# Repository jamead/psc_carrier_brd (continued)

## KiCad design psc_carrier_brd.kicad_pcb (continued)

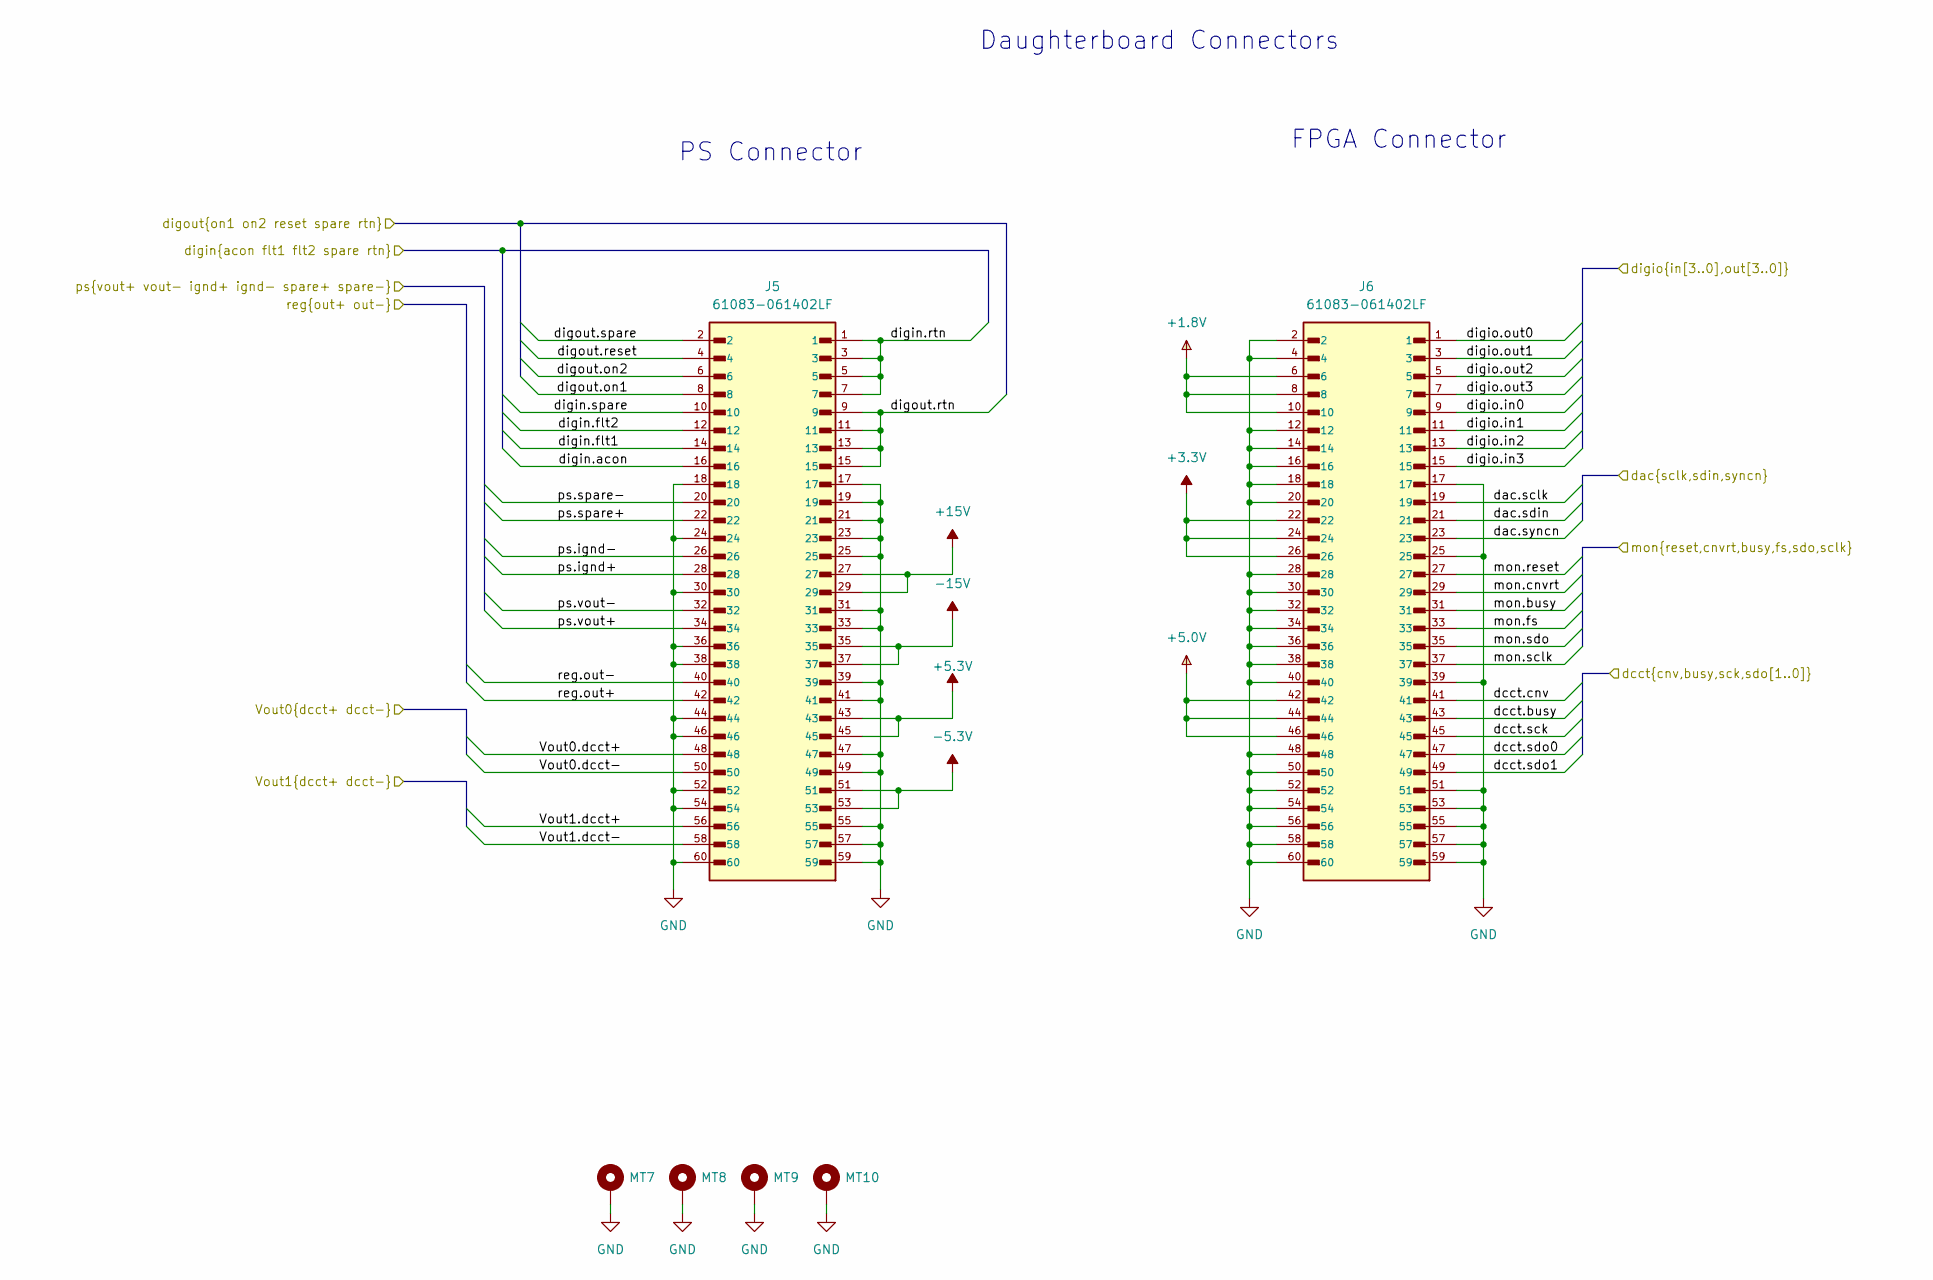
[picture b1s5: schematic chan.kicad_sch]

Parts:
J5, J6: 61083-061402LF; AMPHENOL_61083-061402LF; PARTREV AT
MT7, MT8, MT9, MT10: MountingHole_Pad; MountingHole_3.2mm_M3_Pad_TopBottom

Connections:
+1.8V: J6.6, J6.8, J6.10; also elsewhere on the board
+3.3V: J6.22, J6.24, J6.26; also elsewhere on the board
+5.3V: J5.43, J5.45; also elsewhere on the board
-5.3V: J5.51, J5.53; also elsewhere on the board
/Ch1 Daughterboard/dac.sclk: J6.19; also elsewhere on the board
/Ch1 Daughterboard/dac.sdin: J6.21; also elsewhere on the board
/Ch1 Daughterboard/dac.syncn: J6.23; also elsewhere on the board
/Ch1 Daughterboard/dcct.busy: J6.43; also elsewhere on the board
/Ch1 Daughterboard/dcct.cnv: J6.41; also elsewhere on the board
/Ch1 Daughterboard/dcct.sck: J6.45; also elsewhere on the board
/Ch1 Daughterboard/dcct.sdo0: J6.47; also elsewhere on the board
/Ch1 Daughterboard/dcct.sdo1: J6.49; also elsewhere on the board
/Ch1 Daughterboard/digin.acon: J5.16; also elsewhere on the board
/Ch1 Daughterboard/digin.flt1: J5.14; also elsewhere on the board
/Ch1 Daughterboard/digin.flt2: J5.12; also elsewhere on the board
/Ch1 Daughterboard/digin.rtn: J5.1, J5.3, J5.5, J5.7; also elsewhere on the board
/Ch1 Daughterboard/digin.spare: J5.10; also elsewhere on the board
/Ch1 Daughterboard/digio.in0: J6.9; also elsewhere on the board
/Ch1 Daughterboard/digio.in1: J6.11; also elsewhere on the board
/Ch1 Daughterboard/digio.in2: J6.13; also elsewhere on the board
/Ch1 Daughterboard/digio.in3: J6.15; also elsewhere on the board
/Ch1 Daughterboard/digio.out0: J6.1; also elsewhere on the board
/Ch1 Daughterboard/digio.out1: J6.3; also elsewhere on the board
/Ch1 Daughterboard/digio.out2: J6.5; also elsewhere on the board
/Ch1 Daughterboard/digio.out3: J6.7; also elsewhere on the board
/Ch1 Daughterboard/digout.on1: J5.8; also elsewhere on the board
/Ch1 Daughterboard/digout.on2: J5.6; also elsewhere on the board
/Ch1 Daughterboard/digout.reset: J5.4; also elsewhere on the board
/Ch1 Daughterboard/digout.rtn: J5.9, J5.11, J5.13, J5.15; also elsewhere on the board
/Ch1 Daughterboard/digout.spare: J5.2; also elsewhere on the board
/Ch1 Daughterboard/mon.busy: J6.31; also elsewhere on the board
/Ch1 Daughterboard/mon.cnvrt: J6.29; also elsewhere on the board
/Ch1 Daughterboard/mon.fs: J6.33; also elsewhere on the board
/Ch1 Daughterboard/mon.reset: J6.27; also elsewhere on the board
/Ch1 Daughterboard/mon.sclk: J6.37; also elsewhere on the board
/Ch1 Daughterboard/mon.sdo: J6.35; also elsewhere on the board
/Ch1 Daughterboard/ps.ignd+: J5.28; also elsewhere on the board
/Ch1 Daughterboard/ps.ignd-: J5.26; also elsewhere on the board
/Ch1 Daughterboard/ps.spare+: J5.22; also elsewhere on the board
/Ch1 Daughterboard/ps.spare-: J5.20; also elsewhere on the board
/Ch1 Daughterboard/ps.vout+: J5.34; also elsewhere on the board
/Ch1 Daughterboard/ps.vout-: J5.32; also elsewhere on the board
/Ch1 Daughterboard/reg.out+: J5.42; also elsewhere on the board
/Ch1 Daughterboard/reg.out-: J5.40; also elsewhere on the board

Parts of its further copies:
J9, J10, J12, J13, J15, J16: 61083-061402LF; AMPHENOL_61083-061402LF; PARTREV AT
MT11, MT12, MT13, MT14, MT15, MT16, MT17, MT18, MT19, MT20, MT21, MT22: MountingHole_Pad; MountingHole_3.2mm_M3_Pad_TopBottom

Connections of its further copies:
+1.8V: J10.6, J10.8, J10.10, J13.6, J13.8, J13.10, J16.6, J16.8, J16.10; also elsewhere on the board
+3.3V: J10.22, J10.24, J10.26, J13.22, J13.24, J13.26, J16.22, J16.24, J16.26; also elsewhere on the board
+5.3V: J9.43, J9.45, J12.43, J12.45, J15.43, J15.45; also elsewhere on the board
-5.3V: J9.51, J9.53, J12.51, J12.53, J15.51, J15.53; also elsewhere on the board
/Ch2 Burden Resistor/Vout0.dcct+: J9.48; also elsewhere on the board
/Ch2 Burden Resistor/Vout0.dcct-: J9.50; also elsewhere on the board
/Ch2 Burden Resistor/Vout1.dcct+: J9.56; also elsewhere on the board
/Ch2 Burden Resistor/Vout1.dcct-: J9.58; also elsewhere on the board
/Ch2 Daughterboard/dac.sclk: J10.19; also elsewhere on the board
/Ch2 Daughterboard/dac.sdin: J10.21; also elsewhere on the board
/Ch2 Daughterboard/dac.syncn: J10.23; also elsewhere on the board
/Ch2 Daughterboard/dcct.busy: J10.43; also elsewhere on the board
/Ch2 Daughterboard/dcct.cnv: J10.41; also elsewhere on the board
/Ch2 Daughterboard/dcct.sck: J10.45; also elsewhere on the board
/Ch2 Daughterboard/dcct.sdo0: J10.47; also elsewhere on the board
/Ch2 Daughterboard/dcct.sdo1: J10.49; also elsewhere on the board
/Ch2 Daughterboard/digin.acon: J9.16; also elsewhere on the board
/Ch2 Daughterboard/digin.flt1: J9.14; also elsewhere on the board
/Ch2 Daughterboard/digin.flt2: J9.12; also elsewhere on the board
/Ch2 Daughterboard/digin.rtn: J9.1, J9.3, J9.5, J9.7; also elsewhere on the board
/Ch2 Daughterboard/digin.spare: J9.10; also elsewhere on the board
/Ch2 Daughterboard/digio.in0: J10.9; also elsewhere on the board
/Ch2 Daughterboard/digio.in1: J10.11; also elsewhere on the board
/Ch2 Daughterboard/digio.in2: J10.13; also elsewhere on the board
/Ch2 Daughterboard/digio.in3: J10.15; also elsewhere on the board
/Ch2 Daughterboard/digio.out0: J10.1; also elsewhere on the board
/Ch2 Daughterboard/digio.out1: J10.3; also elsewhere on the board
/Ch2 Daughterboard/digio.out2: J10.5; also elsewhere on the board
/Ch2 Daughterboard/digio.out3: J10.7; also elsewhere on the board
/Ch2 Daughterboard/digout.on1: J9.8; also elsewhere on the board
/Ch2 Daughterboard/digout.on2: J9.6; also elsewhere on the board
/Ch2 Daughterboard/digout.reset: J9.4; also elsewhere on the board
/Ch2 Daughterboard/digout.rtn: J9.9, J9.11, J9.13, J9.15; also elsewhere on the board
/Ch2 Daughterboard/digout.spare: J9.2; also elsewhere on the board
/Ch2 Daughterboard/mon.busy: J10.31; also elsewhere on the board
/Ch2 Daughterboard/mon.cnvrt: J10.29; also elsewhere on the board
/Ch2 Daughterboard/mon.fs: J10.33; also elsewhere on the board
/Ch2 Daughterboard/mon.reset: J10.27; also elsewhere on the board
/Ch2 Daughterboard/mon.sclk: J10.37; also elsewhere on the board
/Ch2 Daughterboard/mon.sdo: J10.35; also elsewhere on the board
/Ch2 Daughterboard/ps.ignd+: J9.28; also elsewhere on the board
/Ch2 Daughterboard/ps.ignd-: J9.26; also elsewhere on the board
/Ch2 Daughterboard/ps.spare+: J9.22; also elsewhere on the board
/Ch2 Daughterboard/ps.spare-: J9.20; also elsewhere on the board
/Ch2 Daughterboard/ps.vout+: J9.34; also elsewhere on the board
/Ch2 Daughterboard/ps.vout-: J9.32; also elsewhere on the board
/Ch2 Daughterboard/reg.out+: J9.42; also elsewhere on the board
/Ch2 Daughterboard/reg.out-: J9.40; also elsewhere on the board
/Ch3 Burden Resistor/Vout0.dcct+: J12.48; also elsewhere on the board
/Ch3 Burden Resistor/Vout0.dcct-: J12.50; also elsewhere on the board
/Ch3 Burden Resistor/Vout1.dcct+: J12.56; also elsewhere on the board
/Ch3 Burden Resistor/Vout1.dcct-: J12.58; also elsewhere on the board
/Ch3 Daughterboard/dac.sclk: J13.19; also elsewhere on the board
/Ch3 Daughterboard/dac.sdin: J13.21; also elsewhere on the board
/Ch3 Daughterboard/dac.syncn: J13.23; also elsewhere on the board
/Ch3 Daughterboard/dcct.busy: J13.43; also elsewhere on the board
/Ch3 Daughterboard/dcct.cnv: J13.41; also elsewhere on the board
/Ch3 Daughterboard/dcct.sck: J13.45; also elsewhere on the board
/Ch3 Daughterboard/dcct.sdo0: J13.47; also elsewhere on the board
/Ch3 Daughterboard/dcct.sdo1: J13.49; also elsewhere on the board
/Ch3 Daughterboard/digin.acon: J12.16; also elsewhere on the board
/Ch3 Daughterboard/digin.flt1: J12.14; also elsewhere on the board
/Ch3 Daughterboard/digin.flt2: J12.12; also elsewhere on the board
/Ch3 Daughterboard/digin.rtn: J12.1, J12.3, J12.5, J12.7; also elsewhere on the board
/Ch3 Daughterboard/digin.spare: J12.10; also elsewhere on the board
/Ch3 Daughterboard/digio.in0: J13.9; also elsewhere on the board
/Ch3 Daughterboard/digio.in1: J13.11; also elsewhere on the board
/Ch3 Daughterboard/digio.in2: J13.13; also elsewhere on the board
/Ch3 Daughterboard/digio.in3: J13.15; also elsewhere on the board
/Ch3 Daughterboard/digio.out0: J13.1; also elsewhere on the board
/Ch3 Daughterboard/digio.out1: J13.3; also elsewhere on the board
/Ch3 Daughterboard/digio.out2: J13.5; also elsewhere on the board
/Ch3 Daughterboard/digio.out3: J13.7; also elsewhere on the board
/Ch3 Daughterboard/digout.on1: J12.8; also elsewhere on the board
/Ch3 Daughterboard/digout.on2: J12.6; also elsewhere on the board
/Ch3 Daughterboard/digout.reset: J12.4; also elsewhere on the board
/Ch3 Daughterboard/digout.rtn: J12.9, J12.11, J12.13, J12.15; also elsewhere on the board
/Ch3 Daughterboard/digout.spare: J12.2; also elsewhere on the board
/Ch3 Daughterboard/mon.busy: J13.31; also elsewhere on the board
/Ch3 Daughterboard/mon.cnvrt: J13.29; also elsewhere on the board
/Ch3 Daughterboard/mon.fs: J13.33; also elsewhere on the board
/Ch3 Daughterboard/mon.reset: J13.27; also elsewhere on the board
/Ch3 Daughterboard/mon.sclk: J13.37; also elsewhere on the board
/Ch3 Daughterboard/mon.sdo: J13.35; also elsewhere on the board
/Ch3 Daughterboard/ps.ignd+: J12.28; also elsewhere on the board
/Ch3 Daughterboard/ps.ignd-: J12.26; also elsewhere on the board
/Ch3 Daughterboard/ps.spare+: J12.22; also elsewhere on the board
/Ch3 Daughterboard/ps.spare-: J12.20; also elsewhere on the board
/Ch3 Daughterboard/ps.vout+: J12.34; also elsewhere on the board
/Ch3 Daughterboard/ps.vout-: J12.32; also elsewhere on the board
/Ch3 Daughterboard/reg.out+: J12.42; also elsewhere on the board
/Ch3 Daughterboard/reg.out-: J12.40; also elsewhere on the board
/Ch4 Burden Resistor/Vout0.dcct+: J15.48; also elsewhere on the board
/Ch4 Burden Resistor/Vout0.dcct-: J15.50; also elsewhere on the board
/Ch4 Burden Resistor/Vout1.dcct+: J15.56; also elsewhere on the board
/Ch4 Burden Resistor/Vout1.dcct-: J15.58; also elsewhere on the board
/Ch4 Daughterboard/dac.sclk: J16.19; also elsewhere on the board
/Ch4 Daughterboard/dac.sdin: J16.21; also elsewhere on the board
/Ch4 Daughterboard/dac.syncn: J16.23; also elsewhere on the board
/Ch4 Daughterboard/dcct.busy: J16.43; also elsewhere on the board
/Ch4 Daughterboard/dcct.cnv: J16.41; also elsewhere on the board
/Ch4 Daughterboard/dcct.sck: J16.45; also elsewhere on the board
/Ch4 Daughterboard/dcct.sdo0: J16.47; also elsewhere on the board
/Ch4 Daughterboard/dcct.sdo1: J16.49; also elsewhere on the board
/Ch4 Daughterboard/digin.acon: J15.16; also elsewhere on the board
/Ch4 Daughterboard/digin.flt1: J15.14; also elsewhere on the board
/Ch4 Daughterboard/digin.flt2: J15.12; also elsewhere on the board
/Ch4 Daughterboard/digin.rtn: J15.1, J15.3, J15.5, J15.7; also elsewhere on the board
/Ch4 Daughterboard/digin.spare: J15.10; also elsewhere on the board
/Ch4 Daughterboard/digio.in0: J16.9; also elsewhere on the board
/Ch4 Daughterboard/digio.in1: J16.11; also elsewhere on the board
/Ch4 Daughterboard/digio.in2: J16.13; also elsewhere on the board
/Ch4 Daughterboard/digio.in3: J16.15; also elsewhere on the board
/Ch4 Daughterboard/digio.out0: J16.1; also elsewhere on the board
/Ch4 Daughterboard/digio.out1: J16.3; also elsewhere on the board
/Ch4 Daughterboard/digio.out2: J16.5; also elsewhere on the board
/Ch4 Daughterboard/digio.out3: J16.7; also elsewhere on the board
/Ch4 Daughterboard/digout.on1: J15.8; also elsewhere on the board
/Ch4 Daughterboard/digout.on2: J15.6; also elsewhere on the board
/Ch4 Daughterboard/digout.reset: J15.4; also elsewhere on the board
/Ch4 Daughterboard/digout.rtn: J15.9, J15.11, J15.13, J15.15; also elsewhere on the board
/Ch4 Daughterboard/digout.spare: J15.2; also elsewhere on the board
/Ch4 Daughterboard/mon.busy: J16.31; also elsewhere on the board
/Ch4 Daughterboard/mon.cnvrt: J16.29; also elsewhere on the board
/Ch4 Daughterboard/mon.fs: J16.33; also elsewhere on the board
/Ch4 Daughterboard/mon.reset: J16.27; also elsewhere on the board
/Ch4 Daughterboard/mon.sclk: J16.37; also elsewhere on the board
/Ch4 Daughterboard/mon.sdo: J16.35; also elsewhere on the board
/Ch4 Daughterboard/ps.ignd+: J15.28; also elsewhere on the board
/Ch4 Daughterboard/ps.ignd-: J15.26; also elsewhere on the board
/Ch4 Daughterboard/ps.spare+: J15.22; also elsewhere on the board
/Ch4 Daughterboard/ps.spare-: J15.20; also elsewhere on the board
/Ch4 Daughterboard/ps.vout+: J15.34; also elsewhere on the board
/Ch4 Daughterboard/ps.vout-: J15.32; also elsewhere on the board
/Ch4 Daughterboard/reg.out+: J15.42; also elsewhere on the board
/Ch4 Daughterboard/reg.out-: J15.40; also elsewhere on the board

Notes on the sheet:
Daughterboard Connectors
FPGA Connector
PS Connector

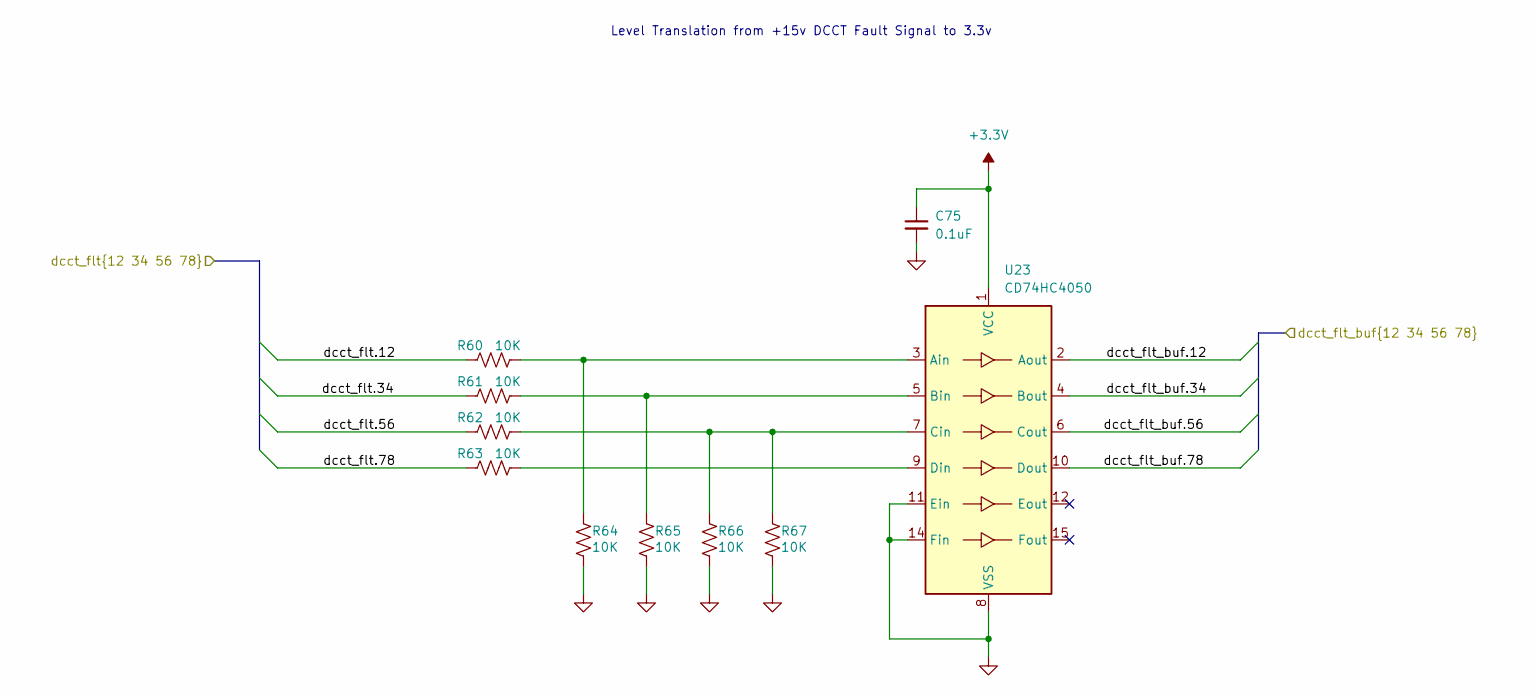
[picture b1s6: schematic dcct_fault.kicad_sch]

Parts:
C75: 0.1uF; C_0402_1005Metric
R60, R61, R62, R63, R64, R65, R66, R67: 10K; R_0402_1005Metric; Tolerance 1%
U23: CD74HC4050; PW16; MFG_PN CD74HC4050PWR

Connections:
+3.3V: C75.1, U23.1 (VCC); also elsewhere on the board
/DCCT Fault Logic/dcct_flt.12: R60.1; also elsewhere on the board
/DCCT Fault Logic/dcct_flt.34: R61.1; also elsewhere on the board
/DCCT Fault Logic/dcct_flt.56: R62.1; also elsewhere on the board
/DCCT Fault Logic/dcct_flt.78: R63.1; also elsewhere on the board
/DCCT Fault Logic/dcct_flt_buf.12: U23.2 (Aout); also elsewhere on the board
/DCCT Fault Logic/dcct_flt_buf.34: U23.4 (Bout); also elsewhere on the board
/DCCT Fault Logic/dcct_flt_buf.56: U23.6 (Cout); also elsewhere on the board
/DCCT Fault Logic/dcct_flt_buf.78: U23.10 (Dout); also elsewhere on the board
unnamed: R60.2, R64.1, U23.3 (Ain)
unnamed: R61.2, R65.1, U23.5 (Bin)
unnamed: R62.2, R66.1, R67.1, U23.7 (Cin)
unnamed: R63.2, U23.9 (Din)

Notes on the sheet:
Level Translation from +15v DCCT Fault Signal to 3.3v

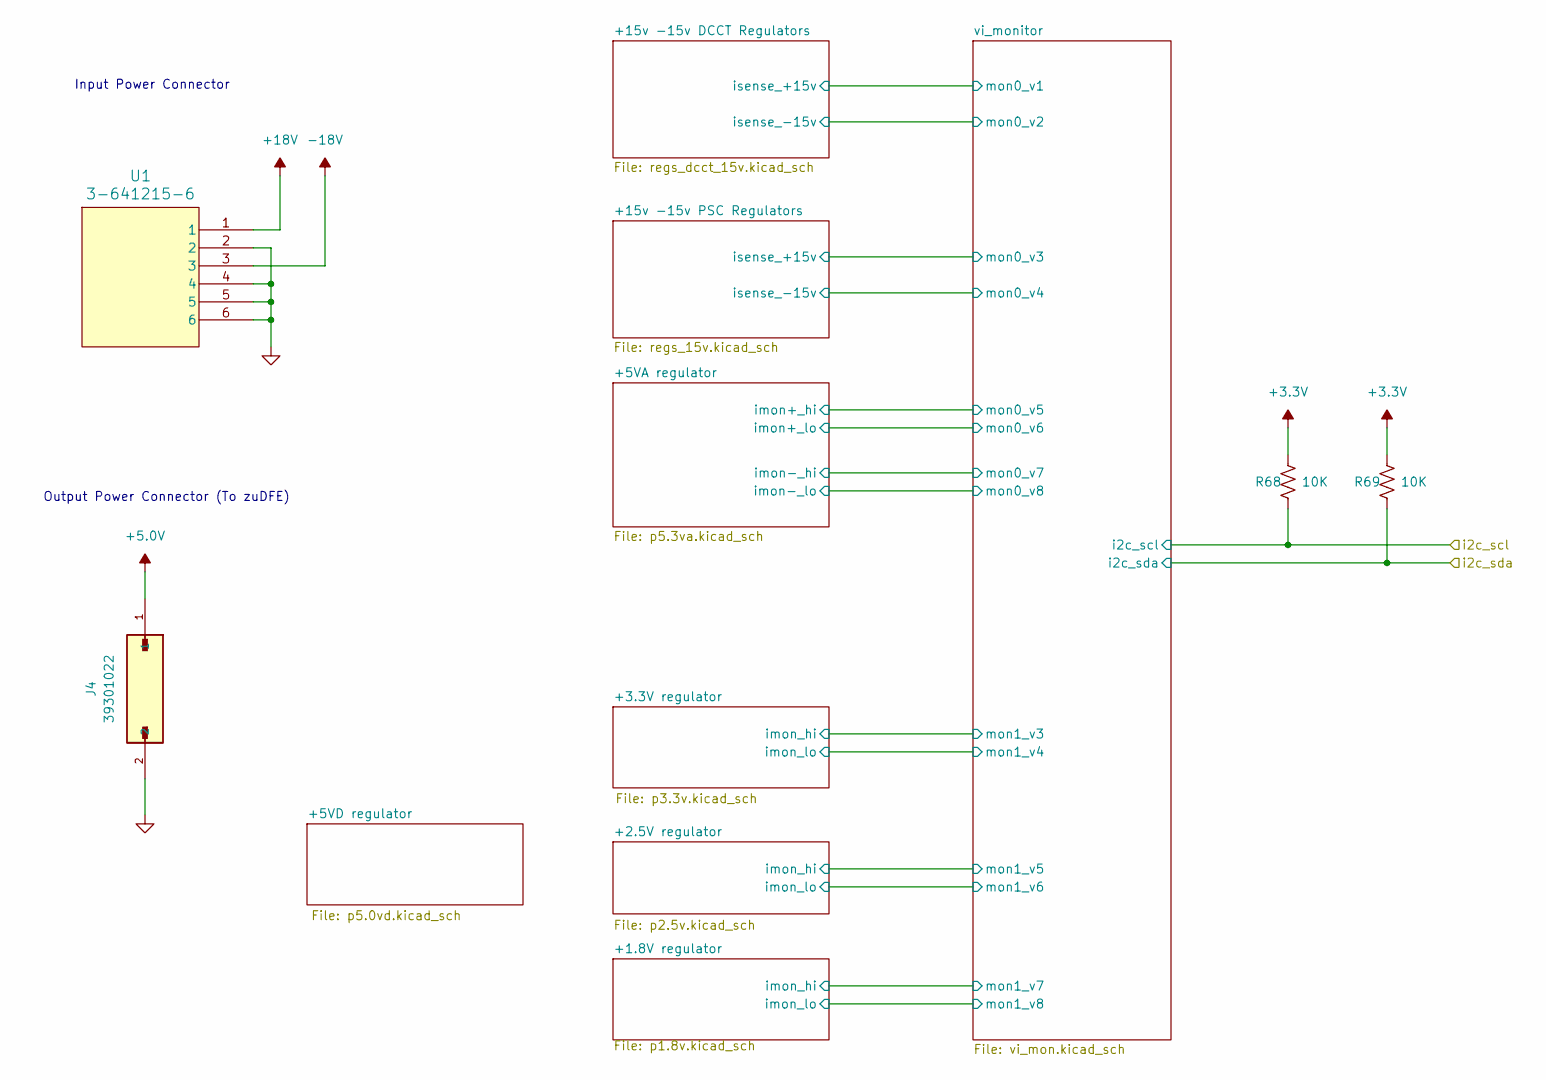
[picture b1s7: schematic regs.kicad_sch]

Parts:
J4: 39301022; MOLEX_39301022; PARTREV A
R68, R69: 10K; R_0402_1005Metric; Tolerance 1%
U1: 3-641215-6; 3-641215-6_TYC

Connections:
+3.3V: R68.1, R69.1; also elsewhere on the board
/regulators/i2c_scl: R68.2; also elsewhere on the board
/regulators/i2c_sda: R69.2; also elsewhere on the board

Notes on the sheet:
Output Power Connector (To zuDFE)
Input Power Connector

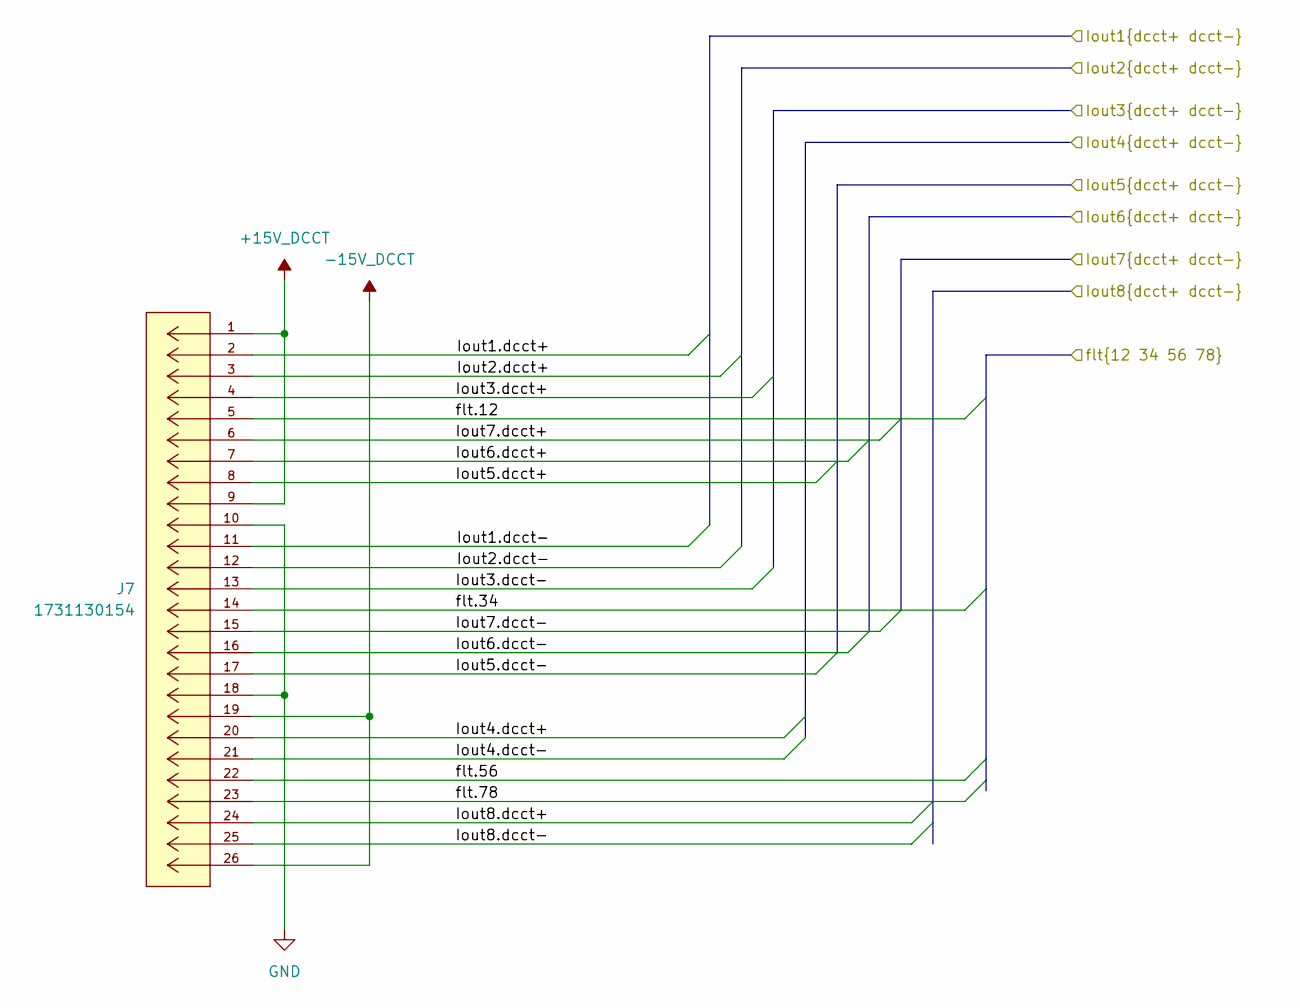
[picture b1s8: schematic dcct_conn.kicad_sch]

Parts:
J7: 1731130154; CONN_F15-26P135G0-5979_MOL; MANUFACTURER_PART_NUMBER 1731130154

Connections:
+15V_DCCT: J7.1, J7.9; also elsewhere on the board
-15V_DCCT: J7.19, J7.26; also elsewhere on the board
/Ch1 Burden Resistor/Iin0.dcct-: J7.11; also elsewhere on the board
/Ch2 Burden Resistor/Iin0.dcct+: J7.4; also elsewhere on the board
/Ch2 Burden Resistor/Iin0.dcct-: J7.13; also elsewhere on the board
/Ch2 Burden Resistor/Iin1.dcct+: J7.20; also elsewhere on the board
/Ch2 Burden Resistor/Iin1.dcct-: J7.21; also elsewhere on the board
/Ch3 Burden Resistor/Iin0.dcct+: J7.8; also elsewhere on the board
/Ch3 Burden Resistor/Iin0.dcct-: J7.17; also elsewhere on the board
/Ch3 Burden Resistor/Iin1.dcct+: J7.7; also elsewhere on the board
/Ch3 Burden Resistor/Iin1.dcct-: J7.16; also elsewhere on the board
/Ch4 Burden Resistor/Iin0.dcct+: J7.6; also elsewhere on the board
/Ch4 Burden Resistor/Iin0.dcct-: J7.15; also elsewhere on the board
/Ch4 Burden Resistor/Iin1.dcct+: J7.24; also elsewhere on the board
/Ch4 Burden Resistor/Iin1.dcct-: J7.25; also elsewhere on the board
/DCCT Fault Logic/dcct_flt.12: J7.5; also elsewhere on the board
/DCCT Fault Logic/dcct_flt.34: J7.14; also elsewhere on the board
/DCCT Fault Logic/dcct_flt.56: J7.22; also elsewhere on the board
/DCCT Fault Logic/dcct_flt.78: J7.23; also elsewhere on the board

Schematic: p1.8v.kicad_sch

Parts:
C34, C35, C38: 10uF; C_0603_1608Metric; Voltage 25V
C36, C37: 0.1uF; C_0402_1005Metric
C39: 100uF; C_1206_3216Metric; Voltage 10V
L4: LSMGG160808T331RG; IND_LSMG_160808_TAY
R20: 0; R_0402_1005Metric; Tolerance 1%
R21: 18.0K; R_0402_1005Metric; Tolerance 1%
R22: KRL2012E-M-R220-F-T5; RESC1220X70N
U9: LT3045xDD; DFN-10-1EP_3x3mm_P0.5mm_EP1.65x2.38mm

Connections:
+1.8V: R22.2, U9.9 (OUTS); also elsewhere on the board
/regulators/+1.8V regulator/imon_hi: C37.1, C38.1, C39.1, R22.1, U9.10 (OUT); also elsewhere on the board
unnamed: C35.1, C36.1, L4.1, U9.1 (IN), U9.2 (IN), U9.3 (EN/UV), U9.6 (PGFB)
unnamed: R20.1, U9.5 (ILIM)
unnamed: R21.1, U9.7 (SET)

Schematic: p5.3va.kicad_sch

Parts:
C16, C17, C18, C20, C22, C25: 10uF; C_0603_1608Metric; Voltage 25V
C19, C21, C23, C24: 0.1uF; C_0402_1005Metric
C26, C27: 100uF; C_1206_3216Metric; Voltage 10V
L1, L2: LSMGG160808T331RG; IND_LSMG_160808_TAY
R11: 0; R_0402_1005Metric; Tolerance 1%
R12: 53K; R_0402_1005Metric; Tolerance 1%
R13, R14: KRL2012E-M-R220-F-T5; RESC1220X70N
R15: 11.4K; R_0402_1005Metric; Tolerance 1%
R16: 1.0K; R_0402_1005Metric; Tolerance 1%
U6: LT3015EDDPBF; DFN-8_DD; MANUFACTURER_PART_NUMBER lt3015edd#pbf
U7: LT3045xDD; DFN-10-1EP_3x3mm_P0.5mm_EP1.65x2.38mm

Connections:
+5.3V: R14.2, U7.9 (OUTS); also elsewhere on the board
-5.3V: R13.2, R15.1; also elsewhere on the board
/regulators/+5VA regulator/+5.3Vout: C23.1, C25.1, C27.1, R14.1, U7.10 (OUT); also elsewhere on the board
/regulators/+5VA regulator/-5.3Vout: C22.1, C24.1, C26.1, R13.1, U6.7 (OUT), U6.8 (OUT); also elsewhere on the board
unnamed: C18.1, C19.1, L1.1, U6.1 (IN), U6.2 (IN), U6.3 (*SHDN), U6.9 (IN)
unnamed: R15.2, R16.1, U6.6 (SENSE/ADJ)
unnamed: C20.1, C21.1, L2.1, U7.1 (IN), U7.2 (IN), U7.3 (EN/UV), U7.6 (PGFB)
unnamed: R11.1, U7.5 (ILIM)
unnamed: R12.1, U7.7 (SET)

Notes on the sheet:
Expected Iout = 9mA*4 + 5mA*4 = 56mA Pd = 56mA * 9.7v = 0.54W deltaT ~ 25 C

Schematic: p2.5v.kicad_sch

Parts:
C40, C41, C44: 10uF; C_0603_1608Metric; Voltage 25V
C42, C43: 0.1uF; C_0402_1005Metric
C45: 100uF; C_1206_3216Metric; Voltage 10V
L5: LSMGG160808T331RG; IND_LSMG_160808_TAY
R23: 0; R_0402_1005Metric; Tolerance 1%
R24: 24.9K; R_0402_1005Metric; Tolerance 1%
R25: KRL2012E-M-R220-F-T5; RESC1220X70N
U10: LT3045xDD; DFN-10-1EP_3x3mm_P0.5mm_EP1.65x2.38mm

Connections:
+2.5V: R25.2, U10.9 (OUTS); also elsewhere on the board
/regulators/+2.5V regulator/imon_hi: C43.1, C44.1, C45.1, R25.1, U10.10 (OUT); also elsewhere on the board
unnamed: C41.1, C42.1, L5.1, U10.1 (IN), U10.2 (IN), U10.3 (EN/UV), U10.6 (PGFB)
unnamed: R23.1, U10.5 (ILIM)
unnamed: R24.1, U10.7 (SET)

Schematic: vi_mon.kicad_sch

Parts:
C57, C58, C59: 0.1uF; C_0402_1005Metric
R36, R38, R40, R43, R45, R47: 9K; R_0402_1005Metric; Tolerance 1%
R37, R39, R41: 1K; R_0402_1005Metric; Tolerance 1%
R42, R44, R46: 9.56K; R_0402_1005Metric; Tolerance 1%
R48, R49: 4.99K; R_0402_1005Metric; Tolerance 1%
U12, U13, U14: LTC2991CMS_TRPBF; MSOP-16_MS; MANUFACTURER_PART_NUMBER ltc2991cms#pbf

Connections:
+1.8V: U12.8 (V8); also elsewhere on the board
+2.5V: U12.6 (V6); also elsewhere on the board
+3.3V: C57.1, C58.1, C59.1, R48.1, R49.1, U12.4 (V4), U12.16 (VCC), U13.16 (VCC), U14.16 (VCC); also elsewhere on the board
+5.3V: U14.6 (V6); also elsewhere on the board
+15V_DCCT: R40.1; also elsewhere on the board
-5.3V: U14.8 (V8); also elsewhere on the board
-15V_DCCT: R46.1; also elsewhere on the board
/regulators/+1.8V regulator/imon_hi: U12.7 (V7); also elsewhere on the board
/regulators/+2.5V regulator/imon_hi: U12.5 (V5); also elsewhere on the board
/regulators/+3.3V regulator/imon_hi: U12.3 (V3); also elsewhere on the board
/regulators/+5VA regulator/+5.3Vout: U14.5 (V5); also elsewhere on the board
/regulators/+5VA regulator/-5.3Vout: U14.7 (V7); also elsewhere on the board
/regulators/+15v -15v DCCT Regulators/isense_+15v: U14.1 (V1); also elsewhere on the board
/regulators/+15v -15v DCCT Regulators/isense_-15v: U14.2 (V2); also elsewhere on the board
/regulators/+15v -15v PSC Regulators/isense_+15v: U14.3 (V3); also elsewhere on the board
/regulators/+15v -15v PSC Regulators/isense_-15v: U14.4 (V4); also elsewhere on the board
/regulators/i2c_scl: U12.11 (SCL), U13.11 (SCL), U14.11 (SCL); also elsewhere on the board
/regulators/i2c_sda: U12.10 (SDA), U13.10 (SDA), U14.10 (SDA); also elsewhere on the board
unnamed: R48.2, U12.13 (ADR0)
unnamed: R49.2, U13.14 (ADR1)
unnamed 247: R38.2, R39.1, U13.2 (V2); also elsewhere on the board
unnamed: R40.2, R41.1, U13.3 (V3)
unnamed: R42.2, R43.1, U13.4 (V4)
unnamed: R44.2, R45.1, U13.5 (V5)
unnamed: R46.2, R47.1, U13.6 (V6)

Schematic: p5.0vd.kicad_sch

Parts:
C61, C62, C65: 10uF; C_0603_1608Metric; Voltage 25V
C63, C64: 0.1uF; C_0402_1005Metric
C66: 100uF; C_1206_3216Metric; Voltage 10V
L6: LSMGG160808T331RG; IND_LSMG_160808_TAY
R36: 0; R_0402_1005Metric; Tolerance 1%
R37: 49.9K; R_0402_1005Metric; Tolerance 1%
R38: KRL2012E-M-R220-F-T5; RESC1220X70N
U15: LT3045xDD; DFN-10-1EP_3x3mm_P0.5mm_EP1.65x2.38mm

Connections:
/Ch1 Burden Resistor/Iin0.dcct-: U15.4 (I-); also elsewhere on the board
unnamed 247: R38.2, U15.9 (OUTS); also elsewhere on the board

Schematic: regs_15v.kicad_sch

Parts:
C1, C2: 100uF; CAP_EEFK_D8_PAN
C3, C4, C9, C11: 10uF; C_0603_1608Metric; Voltage 25V
C5, C6, C10, C12, C13, C14, C15: 0.1uF; C_0402_1005Metric
C7, C8: 100uF; CAPMP7.6X4.3_4.3N_KEM; Part T521X107M025ATE060
R1: 11.4K; R_0402_1005Metric; Tolerance 1%
R2: 1.0K; R_0402_1005Metric; Tolerance 1%
R3, R5, R6, R8: 100; R_0402_1005Metric; Tolerance 1%
R4: KRL6432E-M-R010-F-T1; RES_6432_SUS
R7: 0.01; RES_6432_SUS
R9, R10: 4.99K; R_0402_1005Metric; Tolerance 1%
U2: LT1963AEQ; TO-263-5_TabPin3
U3: LT3015xQ-15; TO-263-5_TabPin3
U4, U5: LT6105; SOT-23-5

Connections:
+5V: C14.1, U4.5 (V+); also elsewhere on the board
/regulators/+15v -15v PSC Regulators/+15V_PSC_REG: C8.1, C11.1, C12.1, C15.1, R1.1, R5.1, R7.2, U2.4 (OUT), U5.5 (V+)
/regulators/+15v -15v PSC Regulators/-15V_PSC_REG: C7.1, C9.1, C10.1, C13.1, R3.1, R4.2, U3.4 (SENSE), U3.5 (OUT), U4.2 (V-)
/regulators/+15v -15v PSC Regulators/isense_+15v: R10.1, U5.1; also elsewhere on the board
/regulators/+15v -15v PSC Regulators/isense_-15v: R9.1, U4.1; also elsewhere on the board
unnamed: R1.2, R2.1, U2.5 (ADJ)
unnamed: R6.2, U4.4 (+)
unnamed: R3.2, U4.3 (-)
unnamed: R5.2, U5.4 (+)
unnamed: R8.2, U5.3 (-)

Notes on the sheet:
Vout=Vense* Rout/Rin (5K/100)

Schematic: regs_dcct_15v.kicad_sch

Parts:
C60, C61: 100uF; CAP_EEFK_D8_PAN
C62, C63, C68, C70: 10uF; C_0603_1608Metric; Voltage 25V
C64, C65, C69, C71, C72, C73, C74: 0.1uF; C_0402_1005Metric
C66, C67: 100uF; CAPMP7.6X4.3_4.3N_KEM; Part T521X107M025ATE060
R50: 11.4K; R_0402_1005Metric; Tolerance 1%
R51: 1.0K; R_0402_1005Metric; Tolerance 1%
R52, R54, R55, R57: 100; R_0402_1005Metric; Tolerance 1%
R53, R56: KRL6432E-M-R010-F-T1; RES_6432_SUS
R58, R59: 4.99K; R_0402_1005Metric; Tolerance 1%
U19: LT1963AEQ; TO-263-5_TabPin3
U20: LT3015xQ-15; TO-263-5_TabPin3
U21, U22: LT6105; SOT-23-5

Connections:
+5V: C73.1, U21.5 (V+); also elsewhere on the board
+15V_DCCT: R56.2, R57.1; also elsewhere on the board
-15V_DCCT: R53.1, R55.1; also elsewhere on the board
/regulators/+15v -15v DCCT Regulators/+15V_DCCT_REG: C67.1, C70.1, C71.1, C74.1, R50.1, R54.1, R56.1, U19.4 (OUT), U22.5 (V+)
/regulators/+15v -15v DCCT Regulators/isense_+15v: R59.1, U22.1; also elsewhere on the board
/regulators/+15v -15v DCCT Regulators/isense_-15v: R58.1, U21.1; also elsewhere on the board
unnamed: R50.2, R51.1, U19.5 (ADJ)
unnamed: R55.2, U21.4 (+)
unnamed: R52.2, U21.3 (-)
unnamed: R54.2, U22.4 (+)
unnamed: R57.2, U22.3 (-)

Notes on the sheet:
Vout=Vense* Rout/Rin (5K/100)

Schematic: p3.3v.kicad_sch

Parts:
C28, C29, C32: 10uF; C_0603_1608Metric; Voltage 25V
C30, C31: 0.1uF; C_0402_1005Metric
C33: 100uF; C_1206_3216Metric; Voltage 10V
L3: LSMGG160808T331RG; IND_LSMG_160808_TAY
R17: 0; R_0402_1005Metric; Tolerance 1%
R18: 33.2K; R_0402_1005Metric; Tolerance 1%
R19: KRL2012E-M-R220-F-T5; RESC1220X70N
U8: LT3045xDD; DFN-10-1EP_3x3mm_P0.5mm_EP1.65x2.38mm

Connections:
+3.3V: R19.2, U8.9 (OUTS); also elsewhere on the board
/regulators/+3.3V regulator/imon_hi: C31.1, C32.1, C33.1, R19.1, U8.10 (OUT); also elsewhere on the board
unnamed: C29.1, C30.1, L3.1, U8.1 (IN), U8.2 (IN), U8.3 (EN/UV), U8.6 (PGFB)
unnamed: R17.1, U8.5 (ILIM)
unnamed: R18.1, U8.7 (SET)

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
